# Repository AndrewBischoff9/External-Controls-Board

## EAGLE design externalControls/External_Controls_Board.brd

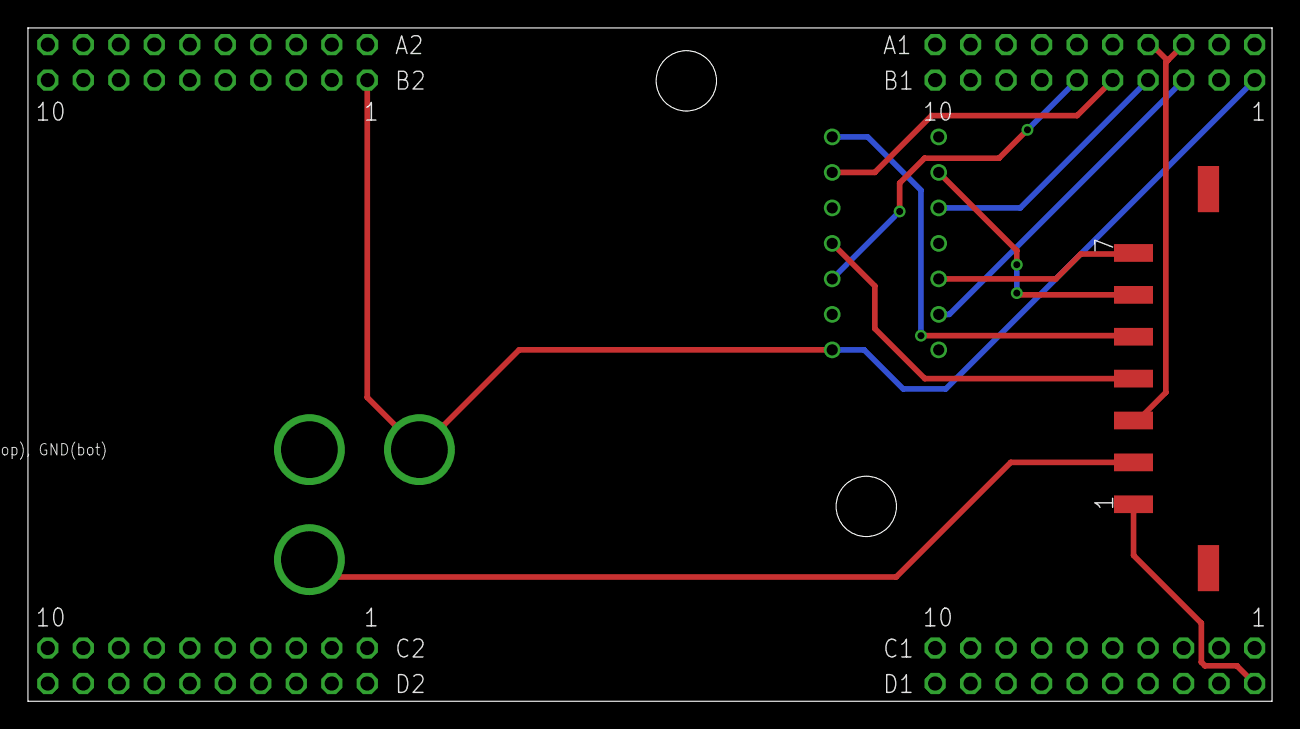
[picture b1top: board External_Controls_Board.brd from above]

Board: 2 copper layers, 89.0 x 48.2 mm, 6 parts (0 on the bottom side), 12 nets.

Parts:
U$1: 74AHCT125; DIP16
U$2: TIVA-C-CONNECTED
U$3: APP_3POS_CONFIG5V_12V_HORIZ; APP45_5V_12V_HORIZ_CONFIG
U$5, U$6: MOUNTING_HOLE#8; #8_SCREW
U$8: MOLEX7-PIN; MOLEX7PIN

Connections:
+5V: U$1.P$14, U$2.+5V_1, U$2.+5V_2, U$3.5V
+12V: U$3.12V, U$8.2
DYNA_DATA: U$2.PC4, U$2.PC5, U$8.3
GND: U$1.P$1, U$1.P$4, U$1.P$7, U$1.P$10, U$1.P$13, U$2.GND_1, U$2.GND_2, U$2.GND_3, U$2.GND_4, U$3.GND, U$8.PAD1
unnamed: U$1.P$3, U$8.7
unnamed: U$1.P$6, U$8.6
unnamed: U$1.P$8, U$8.5
unnamed: U$1.P$11, U$8.4
TIVA_PWM0: U$1.P$2, U$2.PE0
TIVA_PWM1: U$1.P$5, U$2.PE1
TIVA_PWM2: U$1.P$9, U$2.PE2
TIVA_PWM3: U$1.P$12, U$2.PE3

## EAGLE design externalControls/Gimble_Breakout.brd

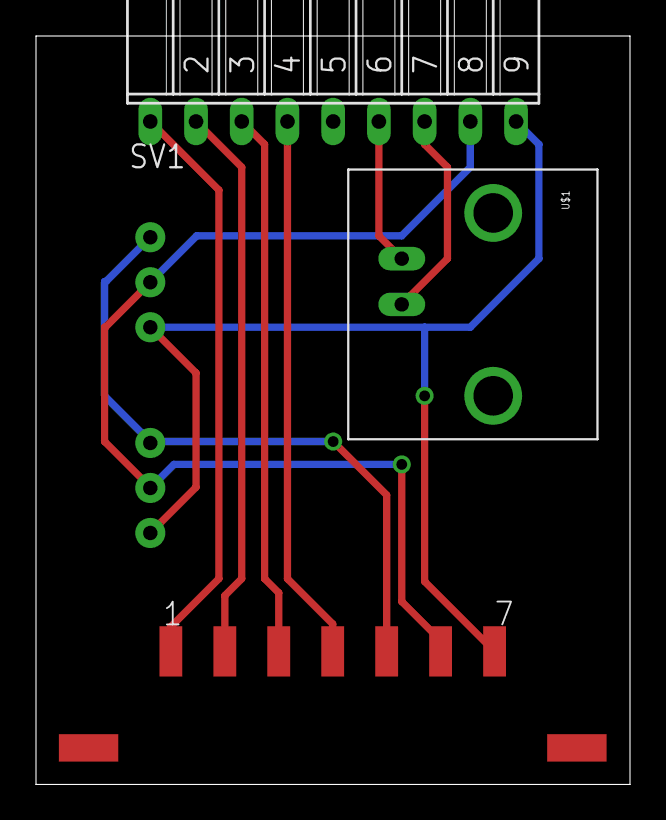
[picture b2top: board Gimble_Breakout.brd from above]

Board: 2 copper layers, 33.0 x 41.6 mm, 5 parts (0 on the bottom side), 9 nets.

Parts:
DYNA1, DYNA2: DYNAMIXEL-1X03HORIZ; MLX-SPOX5268-3PIN
SV1: FE09W
U$1: BNCPTH; BNC
U$2: MOLEX7-PIN; MOLEX7PIN

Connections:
+12V: DYNA1.P$2, DYNA2.P$2, SV1.8, U$2.6
CAM_PWM0: SV1.4, U$2.4
CAM_PWM1: SV1.3, U$2.3
CAM_PWM2: SV1.2, U$2.2
CAM_PWM3: SV1.1, U$2.PAD1
CAM_VIDEO: SV1.7, U$1.S
CAM_VIDEO_GND: SV1.6, U$1.GND
DYNA_DATA: DYNA1.P$3, DYNA2.P$3, U$2.5
GND: DYNA1.P$1, DYNA2.P$1, SV1.9, U$2.7

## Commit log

2016-02-10 :circus_tent: Added .gitattributes & .gitignore files
2016-02-11 First commit
    TODO:
    -double check camera header pin names
    -replace 6-pin header with molex sockets
    -arrange components on board and route it
    -remove xBee stuff for now
2016-02-12 Rev1 Functional
    updated to Rev1 specifications
2016-02-12 Updated Routing
    optimized a few paths

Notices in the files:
parts and their libraries:
SparkFun-Connectors: Licensing: Creative Commons ShareAlike 4.0 International - https://creativecommons.org/licenses/by-sa/4.0
